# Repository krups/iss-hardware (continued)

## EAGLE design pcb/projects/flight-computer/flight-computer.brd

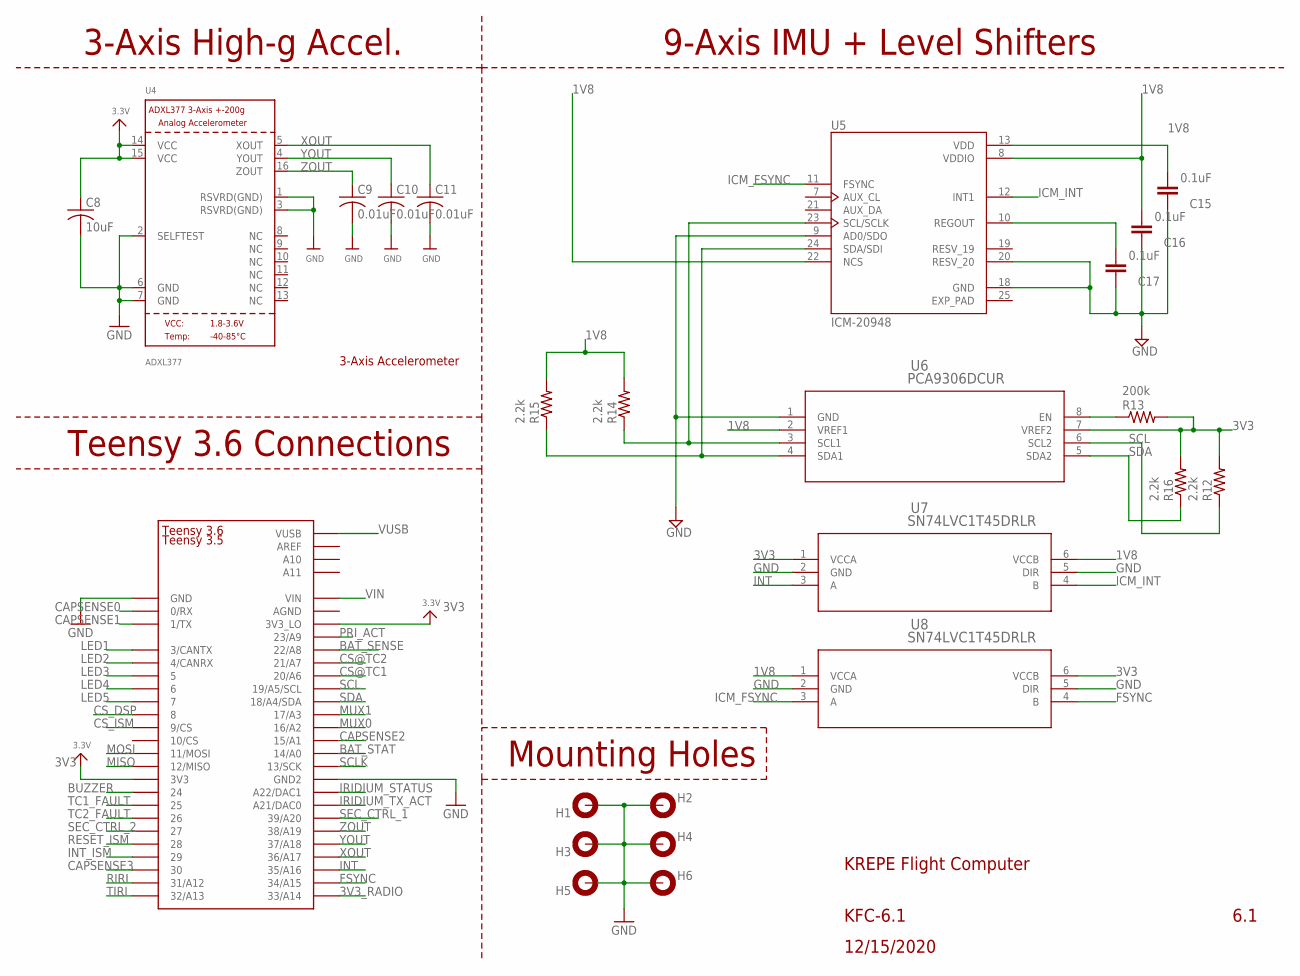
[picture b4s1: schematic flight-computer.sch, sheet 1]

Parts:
C8: 10uF; C0603
C9, C10, C11: 0.01uF; C0603
C15, C16, C17: 0.1uF; C0603
H1, H2, H3, H4, H5, H6: MOUNT-PAD-ROUND2.8; 2,8-PAD
R12, R14, R15, R16: 2.2k; R0603
R13: 200k; R0603
U4: ADXL377; LFCSP16_LQ
U5: ICM-20948; QFN40P300X300X105-25N
U6: PCA9306DCUR; DCU8
U7, U8: SN74LVC1T45DRLR; DRL6
U$1: TEENSY_3.5/3.6_BASIC

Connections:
1V8: C15.2, C16.2, R14.2, R15.2, U5.8 (VDDIO), U5.13 (VDD), U5.22 (NCS), U6.2 (VREF1), U7.6 (VCCB), U8.1 (VCCA); also elsewhere on the board
3V3: C8.1, R12.2, R13.2, R16.2, U4.14 (VCC), U4.15 (VCC), U6.7 (VREF2), U7.1 (VCCA), U8.6 (VCCB), U$1.3V3, U$1.3V3_LO; also elsewhere on the board
3V3_RADIO: U$1.33/A14; also elsewhere on the board
BAT_SENSE: U$1.22/A8; also elsewhere on the board
BAT_STAT: U$1.14/A0; also elsewhere on the board
BUZZER: U$1.24; also elsewhere on the board
CAPSENSE0: U$1.0/RX; also elsewhere on the board
CAPSENSE1: U$1.1/TX; also elsewhere on the board
CAPSENSE2: U$1.15/A1; also elsewhere on the board
CAPSENSE3: U$1.30; also elsewhere on the board
CS@TC1: U$1.20/A6; also elsewhere on the board
CS@TC2: U$1.21/A7; also elsewhere on the board
CS_DSP: U$1.8; also elsewhere on the board
CS_ISM: U$1.9/CS; also elsewhere on the board
EXP_PAD: U5.25 (EXP_PAD)
FSYNC: U8.4 (B), U$1.34/A15
GND: C8.2, C9.2, C10.2, C11.2, C15.1, C16.1, C17.1, H1.B2,8, H2.B2,8, H3.B2,8, H4.B2,8, H5.B2,8, H6.B2,8, U4.1 (RSVRD(GND)), U4.2 (SELFTEST), U4.3 (RSVRD(GND)), U4.6 (GND), U4.7 (GND), U5.9 (AD0/SDO), U5.18 (GND), U5.20 (RESV_20), U6.1 (GND), U7.2 (GND), U7.5 (DIR), U8.2 (GND), U8.5 (DIR), U$1.GND; also elsewhere on the board
ICM_FSYNC: U5.11 (FSYNC), U8.3 (A)
ICM_INT: U5.12 (INT1), U7.4 (B)
INT: U7.3 (A), U$1.35/A16
INT_ISM: U$1.29; also elsewhere on the board
IRIDIUM_STATUS: U$1.A22/DAC1; also elsewhere on the board
IRIDIUM_TX_ACT: U$1.21/DAC0 (A21/DAC0); also elsewhere on the board
LED1: U$1.3/CANTX; also elsewhere on the board
LED2: U$1.4/CANRX; also elsewhere on the board
LED3: U$1.5; also elsewhere on the board
LED4: U$1.6; also elsewhere on the board
LED5: U$1.7; also elsewhere on the board
MISO: U$1.12/MISO; also elsewhere on the board
MOSI: U$1.11/MOSI; also elsewhere on the board
MUX0: U$1.16/A2; also elsewhere on the board
MUX1: U$1.17/A3; also elsewhere on the board
unnamed: R13.1, U6.8 (EN)
unnamed: C17.2, U5.10 (REGOUT)
unnamed: R14.1, U5.23 (SCL/SCLK), U6.3 (SCL1)
unnamed: R15.1, U5.24 (SDA/SDI), U6.4 (SDA1)
PRI_ACT: U$1.23/A9; also elsewhere on the board
RESET_ISM: U$1.28; also elsewhere on the board
RIRI: U$1.31/A12; also elsewhere on the board
SCL: R12.1, U6.6 (SCL2), U$1.19/A5/SCL
SCLK: U$1.13/SCK; also elsewhere on the board
SDA: R16.1, U6.5 (SDA2), U$1.18/A4/SDA
SEC_CTRL_1: U$1.39/A20; also elsewhere on the board
SEC_CTRL_2: U$1.27; also elsewhere on the board
TC1_FAULT: U$1.25; also elsewhere on the board
TC2_FAULT: U$1.26; also elsewhere on the board
TIRI: U$1.32/A13; also elsewhere on the board
VIN: U$1.VIN; also elsewhere on the board
VUSB: U$1.VUSB; also elsewhere on the board
XOUT: C11.1, U4.5 (XOUT), U$1.36/A17
YOUT: C10.1, U4.4 (YOUT), U$1.37/A18
ZOUT: C9.1, U4.16 (ZOUT), U$1.38/A19

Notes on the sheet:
3-Axis Accelerometer
Teensy 3.5
9-Axis IMU + Level Shifters
Teensy 3.6 Connections
3-Axis High-g Accel.
Mounting Holes
KREPE Flight Computer
6.1
KFC-6.1
12/15/2020

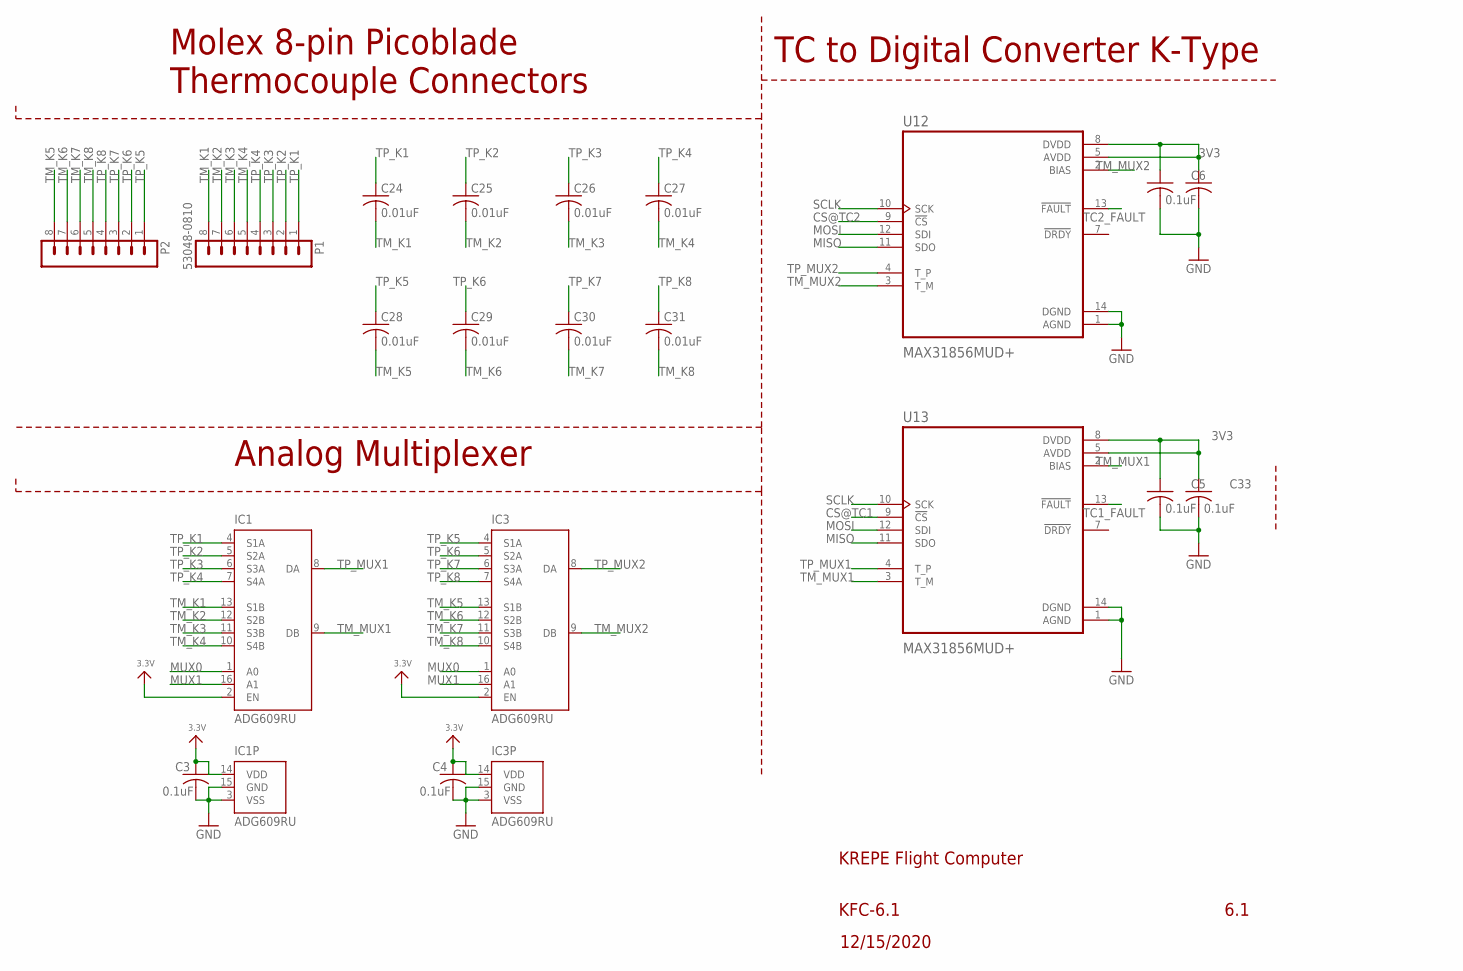
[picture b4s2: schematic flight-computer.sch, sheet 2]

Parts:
C3, C4, C5, C6, C32, C33: 0.1uF; C0603
C24, C25, C26, C27, C28, C29, C30, C31: 0.01uF; C0603
IC1, IC3: ADG609RU; TSSOP16
P1, P2: 53048-0810
U12, U13: MAX31856MUD+; SOP65P640X110-14N

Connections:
3V3: C3.1, C4.1, C5.1, C6.1, C32.1, C33.1, IC1.2 (EN), IC1.14 (VDD), IC3.2 (EN), IC3.14 (VDD), U12.5 (AVDD), U12.8 (DVDD), U13.5 (AVDD), U13.8 (DVDD); also elsewhere on the board
CS@TC1: U13.9 (!CS); also elsewhere on the board
CS@TC2: U12.9 (!CS); also elsewhere on the board
GND: C3.2, C4.2, C5.2, C6.2, C32.2, C33.2, IC1.3 (VSS), IC1.15 (GND), IC3.3 (VSS), IC3.15 (GND), U12.1 (AGND), U12.14 (DGND), U13.1 (AGND), U13.14 (DGND); also elsewhere on the board
MISO: U12.11 (SDO), U13.11 (SDO); also elsewhere on the board
MOSI: U12.12 (SDI), U13.12 (SDI); also elsewhere on the board
MUX0: IC1.1 (A0), IC3.1 (A0); also elsewhere on the board
MUX1: IC1.16 (A1), IC3.16 (A1); also elsewhere on the board
SCLK: U12.10 (SCK), U13.10 (SCK); also elsewhere on the board
TC1_FAULT: U13.13 (!FAULT); also elsewhere on the board
TC2_FAULT: U12.13 (!FAULT); also elsewhere on the board
TM_K1: C24.2, IC1.13 (S1B), P1.8
TM_K2: C25.2, IC1.12 (S2B), P1.7
TM_K3: C26.2, IC1.11 (S3B), P1.6
TM_K4: C27.2, IC1.10 (S4B), P1.5
TM_K5: C28.2, IC3.13 (S1B), P2.8
TM_K6: C29.2, IC3.12 (S2B), P2.7
TM_K7: C30.2, IC3.11 (S3B), P2.6
TM_K8: C31.2, IC3.10 (S4B), P2.5
TM_MUX1: IC1.9 (DB), U13.2 (BIAS), U13.3 (T_M)
TM_MUX2: IC3.9 (DB), U12.2 (BIAS), U12.3 (T_M)
TP_K1: C24.1, IC1.4 (S1A), P1.1
TP_K2: C25.1, IC1.5 (S2A), P1.2
TP_K3: C26.1, IC1.6 (S3A), P1.3
TP_K4: C27.1, IC1.7 (S4A), P1.4
TP_K5: C28.1, IC3.4 (S1A), P2.1
TP_K6: C29.1, IC3.5 (S2A), P2.2
TP_K7: C30.1, IC3.6 (S3A), P2.3
TP_K8: C31.1, IC3.7 (S4A), P2.4
TP_MUX1: IC1.8 (DA), U13.4 (T_P)
TP_MUX2: IC3.8 (DA), U12.4 (T_P)

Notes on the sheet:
Analog Multiplexer
TC to Digital Converter K-Type
Molex 8-pin Picoblade Thermocouple Connectors
6.1
KFC-6.1
12/15/2020
KREPE Flight Computer

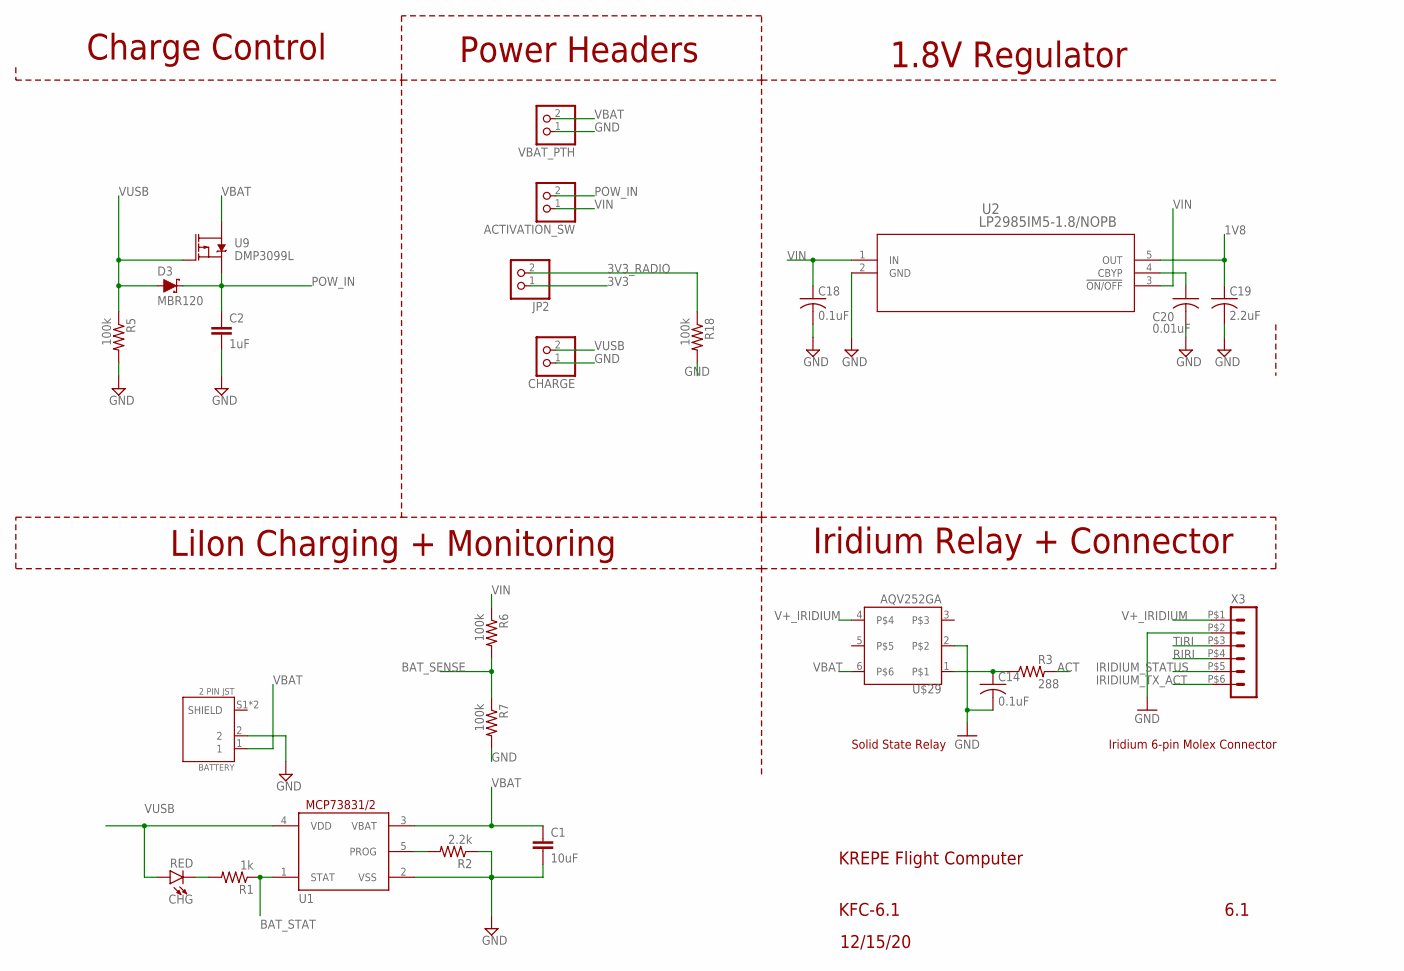
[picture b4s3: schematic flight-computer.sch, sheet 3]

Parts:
ACTIVATION_SW: PINHD-1X2; 1X02
BATTERY: 2 PIN JST; JST_S2B-PH-SM4-TB(LF)(SN)
C1: 10uF; C0603
C2: 1uF; C0603
C14, C18: 0.1uF; C0603
C19: 2.2uF; C0603
C20: 0.01uF; C0603
CHARGE: PINHD-1X2; 1X02
CHG: RED; LED-0603
D3: MBR120; SOD123FL
JP2: PINHD-1X2; 1X02
R1: 1k; R0603
R2: 2.2k; R0603
R3: 288; R0603
R5, R6, R7, R18: 100k; R0603
U1: MCP73831/OT; SOT23-5L
U2: LP2985IM5-1.8/NOPB; MF05A
U9: DMP3099L; SOT23
U$29: AQV252GA; DIP6
VBAT_PTH: PINHD-1X2; 1X02
X3: HEADER_POS6_43650-0600; 43650-0600

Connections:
1V8: C19.1, U2.5 (OUT); also elsewhere on the board
3V3: JP2.1; also elsewhere on the board
3V3_RADIO: JP2.2, R18.1; also elsewhere on the board
ACT: R3.2; also elsewhere on the board
BAT_SENSE: R6.2, R7.1; also elsewhere on the board
BAT_STAT: R1.1, U1.1 (STAT); also elsewhere on the board
GND: BATTERY.2, C1.2, C2.2, C14.2, C18.2, C19.2, C20.2, CHARGE.1, R2.1, R5.2, R7.2, R18.2, U1.2 (VSS), U2.2 (GND), U$29.2, VBAT_PTH.1, X3.P$2 (2); also elsewhere on the board
IRIDIUM_STATUS: X3.P$5 (5); also elsewhere on the board
IRIDIUM_TX_ACT: X3.P$6 (6); also elsewhere on the board
unnamed: R2.2, U1.5 (PROG)
unnamed: C14.1, R3.1, U$29.1
unnamed: CHG.C, R1.2
unnamed: C20.1, U2.4 (CBYP)
POW_IN: ACTIVATION_SW.2, C2.1, D3.C, U9.2 (S)
RIRI: X3.P$4 (4); also elsewhere on the board
TIRI: X3.P$3 (3); also elsewhere on the board
V+_IRIDIUM: U$29.4, X3.P$1 (1)
VBAT: BATTERY.1, C1.1, U1.3 (VBAT), U9.3 (D), U$29.6, VBAT_PTH.2
VIN: ACTIVATION_SW.1, C18.1, R6.1, U2.1 (IN), U2.3 (!ON/OFF); also elsewhere on the board
VUSB: CHARGE.2, CHG.A, D3.A, R5.1, U1.4 (VDD), U9.1 (G); also elsewhere on the board

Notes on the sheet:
Iridium 6-pin Molex Connector
Solid State Relay
Iridium Relay + Connector
Charge Control
Power Headers
LiIon Charging + Monitoring
1.8V Regulator
6.1
KFC-6.1
12/15/20
KREPE Flight Computer

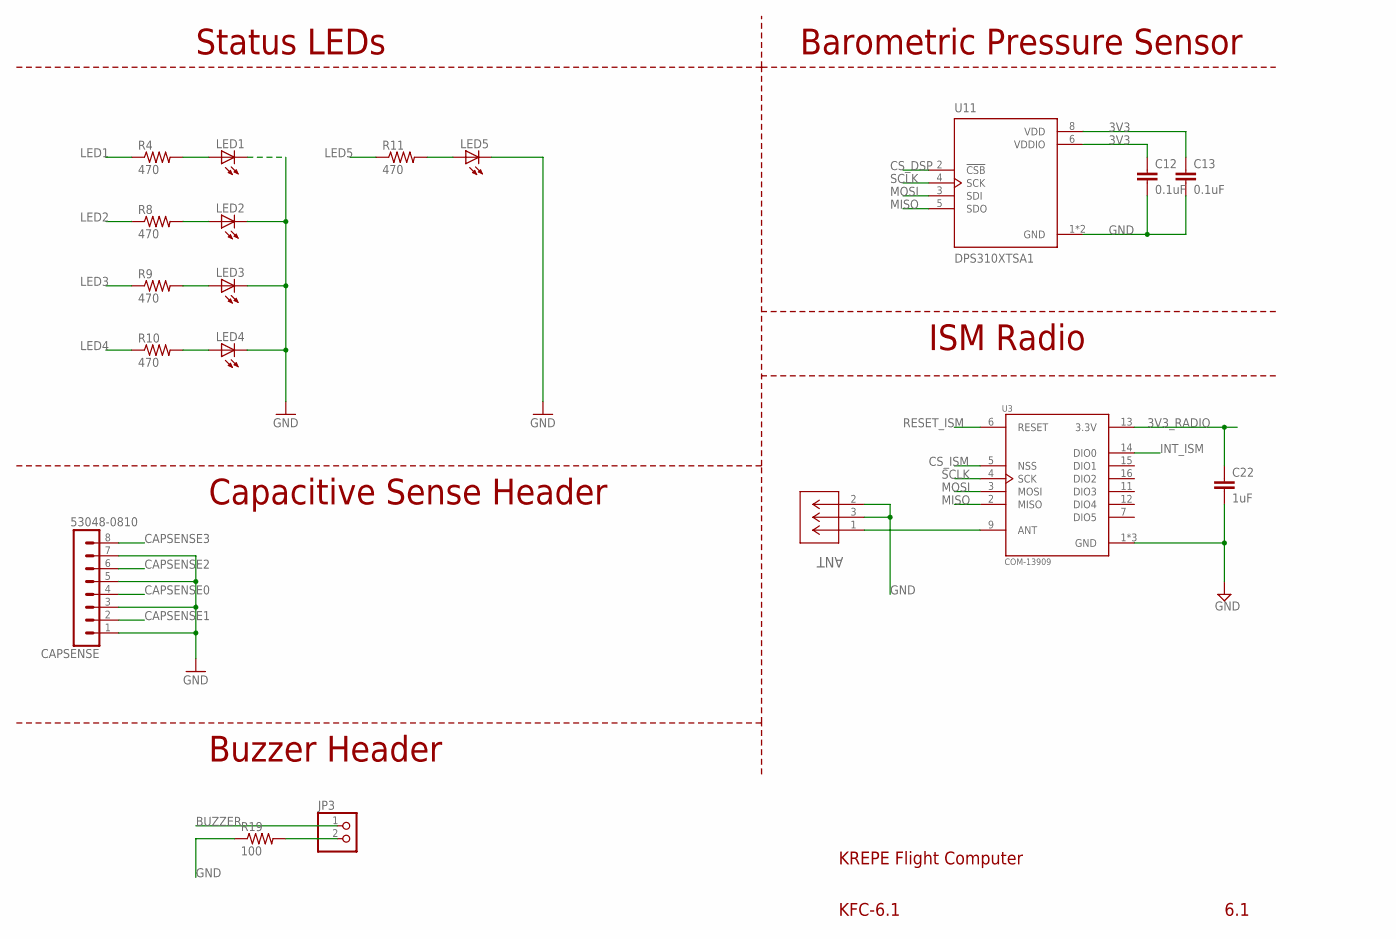
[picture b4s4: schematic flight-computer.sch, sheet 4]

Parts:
ANT: U.FL-R-SMT-1(10); CONN_R-SMT-1(10)
C12, C13: 0.1uF; C0603
C22: 1uF; C0603
CAPSENSE: 53048-0810
JP3: PINHD-1X2; 1X02
LED1, LED2, LED3, LED4, LED5: LEDCHIP-LED0603; CHIP-LED0603
R4, R8, R9, R10, R11: 470; R0603
R19: 100; R0603
U3: COM-13909; MOD_COM-13909
U11: DPS310XTSA1; XDCR_DPS310XTSA1

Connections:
3V3: C12.1, C13.1, U11.6 (VDDIO), U11.8 (VDD); also elsewhere on the board
3V3_RADIO: C22.1, U3.13 (3.3V); also elsewhere on the board
BUZZER: JP3.1; also elsewhere on the board
CAPSENSE0: CAPSENSE.4; also elsewhere on the board
CAPSENSE1: CAPSENSE.2; also elsewhere on the board
CAPSENSE2: CAPSENSE.6; also elsewhere on the board
CAPSENSE3: CAPSENSE.8; also elsewhere on the board
CS_DSP: U11.2 (!CSB); also elsewhere on the board
CS_ISM: U3.5 (NSS); also elsewhere on the board
GND: ANT.2, ANT.3, C12.2, C13.2, C22.2, CAPSENSE.1, CAPSENSE.3, CAPSENSE.5, CAPSENSE.7, LED1.C, LED2.C, LED3.C, LED4.C, LED5.C, R19.1, U3.1 (GND), U3.8 (GND), U3.10 (GND), U11.1 (GND), U11.7 (GND); also elsewhere on the board
INT_ISM: U3.14 (DIO0); also elsewhere on the board
LED1: R4.1; also elsewhere on the board
LED2: R8.1; also elsewhere on the board
LED3: R9.1; also elsewhere on the board
LED4: R10.1; also elsewhere on the board
LED5: R11.1; also elsewhere on the board
MISO: U3.2 (MISO), U11.5 (SDO); also elsewhere on the board
MOSI: U3.3 (MOSI), U11.3 (SDI); also elsewhere on the board
unnamed: JP3.2, R19.2
unnamed: ANT.1, U3.9 (ANT)
unnamed: LED1.A, R4.2
unnamed: LED2.A, R8.2
unnamed: LED3.A, R9.2
unnamed: LED4.A, R10.2
unnamed: LED5.A, R11.2
RESET_ISM: U3.6 (RESET); also elsewhere on the board
SCLK: U3.4 (SCK), U11.4 (SCK); also elsewhere on the board

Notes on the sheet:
ISM Radio
6.1
Status LEDs
Capacitive Sense Header
Buzzer Header
Barometric Pressure Sensor
KFC-6.1
KREPE Flight Computer

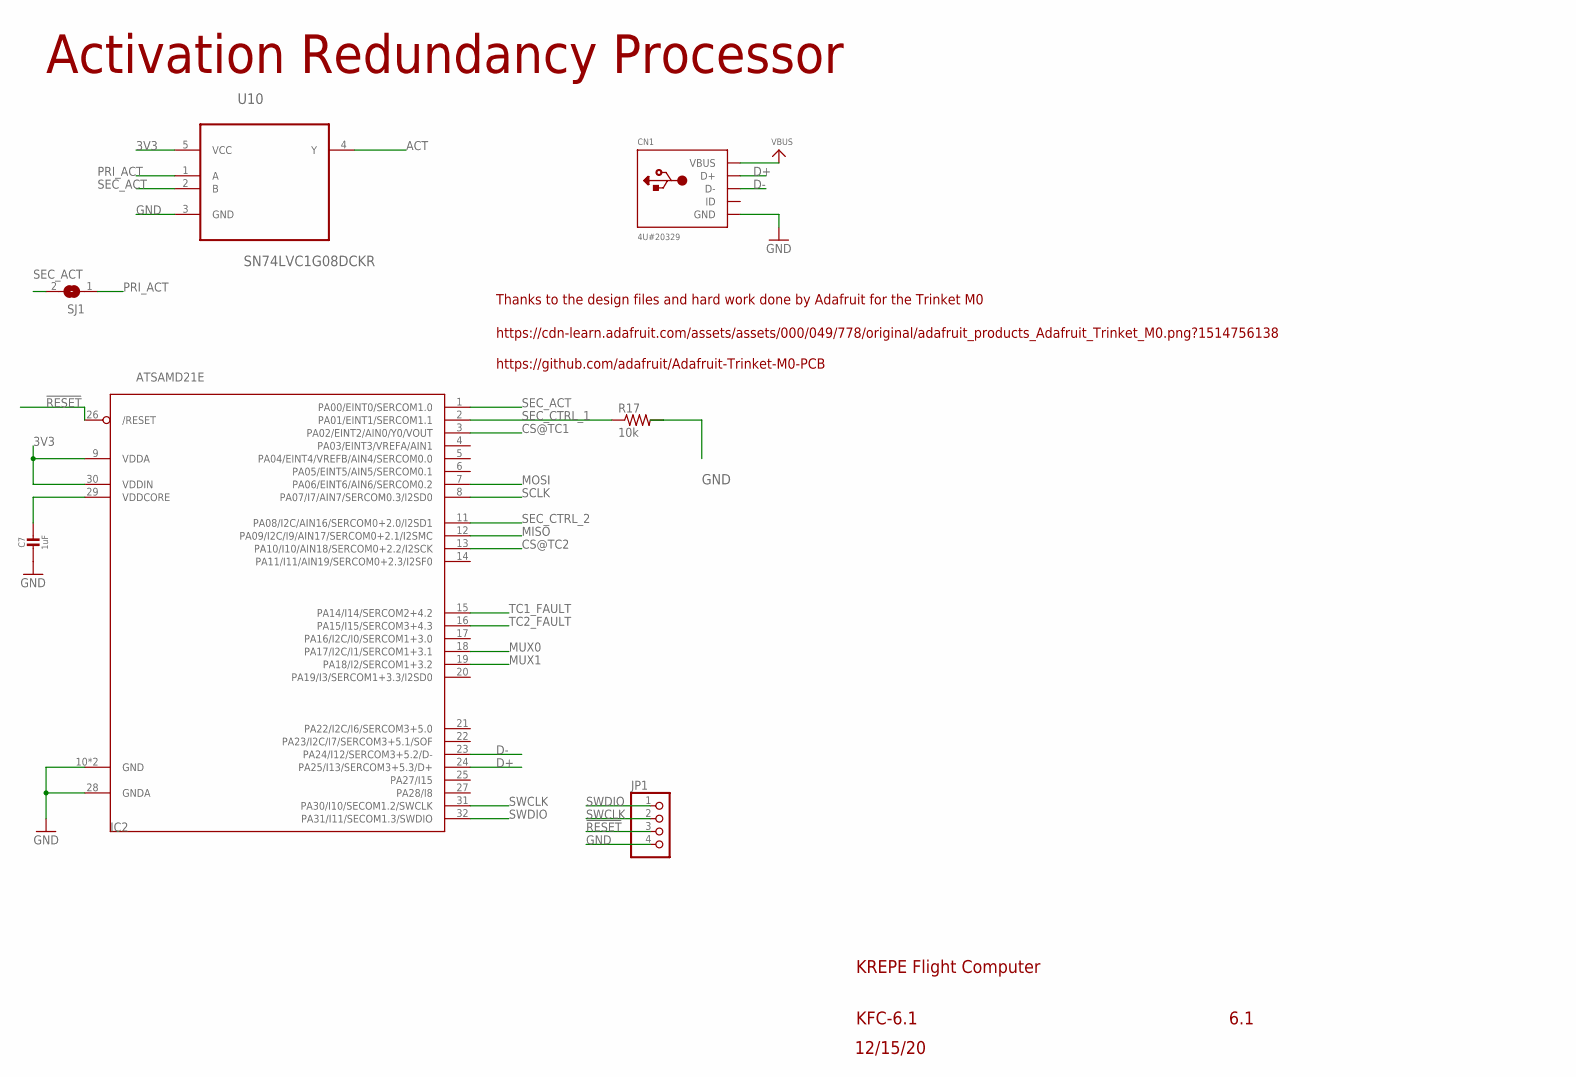
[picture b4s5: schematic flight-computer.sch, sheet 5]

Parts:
C7: 1uF; 0603-NO
CN1: 4U#20329; 4UCONN_20329_V2
IC2: ATSAMD21E; QFN32_5MM
JP1: PINHD-1X4; 1X04
R17: 10k; R0603
SJ1: SJ
U10: SN74LVC1G08DCKR; SOT65P210X110-5N

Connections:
3V3: IC2.9 (VDDA), IC2.30 (VDDIN), U10.5 (VCC); also elsewhere on the board
!RESET: IC2.26 (/RESET), JP1.3
ACT: U10.4 (Y); also elsewhere on the board
CS@TC1: IC2.3 (PA02/EINT2/AIN0/Y0/VOUT); also elsewhere on the board
CS@TC2: IC2.13 (PA10/I10/AIN18/SERCOM0+2.2/I2SCK); also elsewhere on the board
D+: CN1.D+, IC2.24 (PA25/I13/SERCOM3+5.3/D+)
D-: CN1.D-, IC2.23 (PA24/I12/SERCOM3+5.2/D-)
GND: C7.2, CN1.BASE@1 (GND), CN1.BASE@2 (GND), CN1.GND, CN1.SPRT@1 (GND), CN1.SPRT@2 (GND), CN1.SPRT@3 (GND), CN1.SPRT@4 (GND), IC2.10 (GND), IC2.28 (GNDA), IC2.33 (GND), JP1.4, R17.2, U10.3 (GND); also elsewhere on the board
MISO: IC2.12 (PA09/I2C/I9/AIN17/SERCOM0+2.1/I2SMC); also elsewhere on the board
MOSI: IC2.7 (PA06/EINT6/AIN6/SERCOM0.2); also elsewhere on the board
MUX0: IC2.18 (PA17/I2C/I1/SERCOM1+3.1); also elsewhere on the board
MUX1: IC2.19 (PA18/I2/SERCOM1+3.2); also elsewhere on the board
PRI_ACT: SJ1.1, U10.1 (A); also elsewhere on the board
SCLK: IC2.8 (PA07/I7/AIN7/SERCOM0.3/I2SD0); also elsewhere on the board
SEC_ACT: IC2.1 (PA00/EINT0/SERCOM1.0), SJ1.2, U10.2 (B)
SEC_CTRL_1: IC2.2 (PA01/EINT1/SERCOM1.1), R17.1; also elsewhere on the board
SEC_CTRL_2: IC2.11 (PA08/I2C/AIN16/SERCOM0+2.0/I2SD1); also elsewhere on the board
SWCLK: IC2.31 (PA30/I10/SECOM1.2/SWCLK), JP1.2
SWDIO: IC2.32 (PA31/I11/SECOM1.3/SWDIO), JP1.1
TC1_FAULT: IC2.15 (PA14/I14/SERCOM2+4.2); also elsewhere on the board
TC2_FAULT: IC2.16 (PA15/I15/SERCOM3+4.3); also elsewhere on the board
VBUS: CN1.VBUS
VDDCORE1: C7.1, IC2.29 (VDDCORE)

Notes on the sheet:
Activation Redundancy Processor
Thanks to the design files and hard work done by Adafruit for the Trinket M0
https://cdn-learn.adafruit.com/assets/assets/000/049/778/original/adafruit_products_Adafruit_Trinket_M0.png?1514756138 https://github.com/adafruit/Adafruit-Trinket-M0-PCB
KFC-6.1
KREPE Flight Computer
12/15/20
6.1

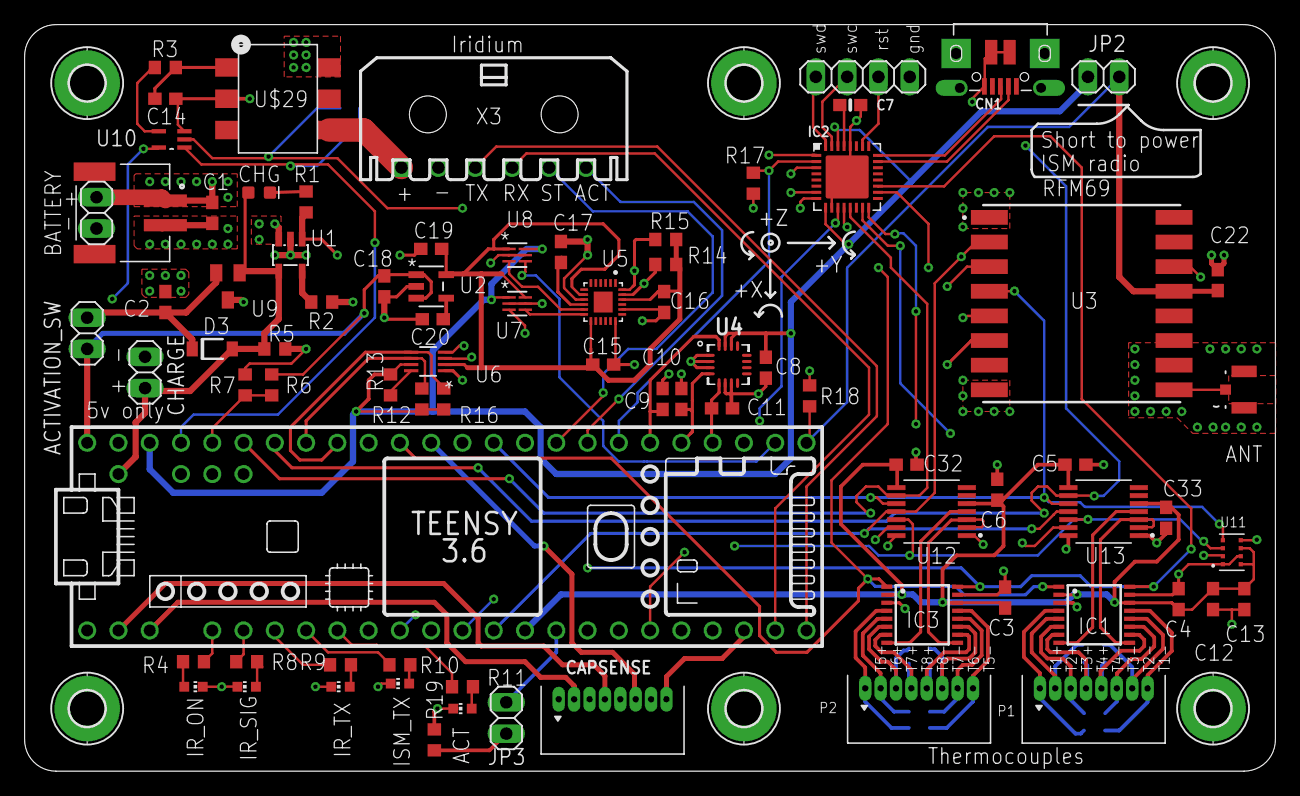
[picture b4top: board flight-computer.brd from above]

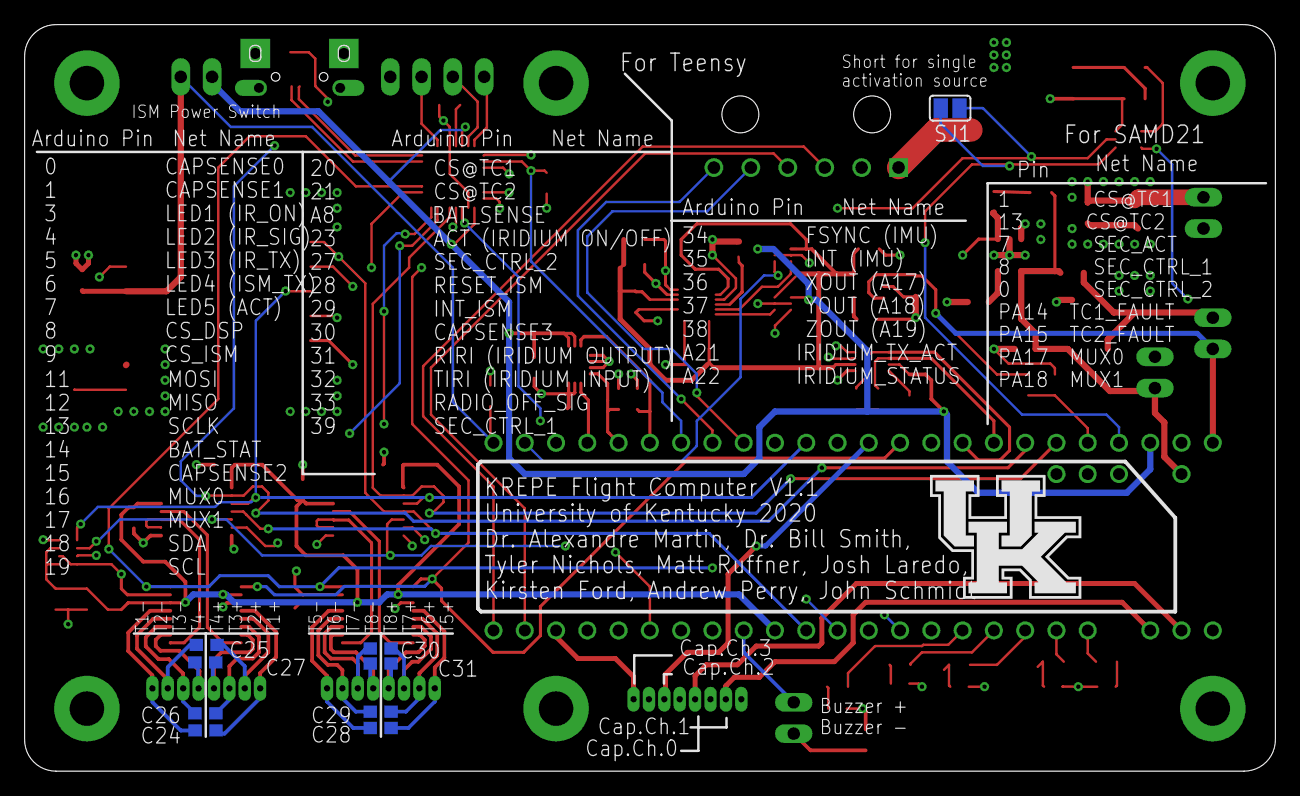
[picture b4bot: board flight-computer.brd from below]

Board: 4 copper layers, 101.6 x 60.6 mm, 95 parts (9 on the bottom side), 93 nets.

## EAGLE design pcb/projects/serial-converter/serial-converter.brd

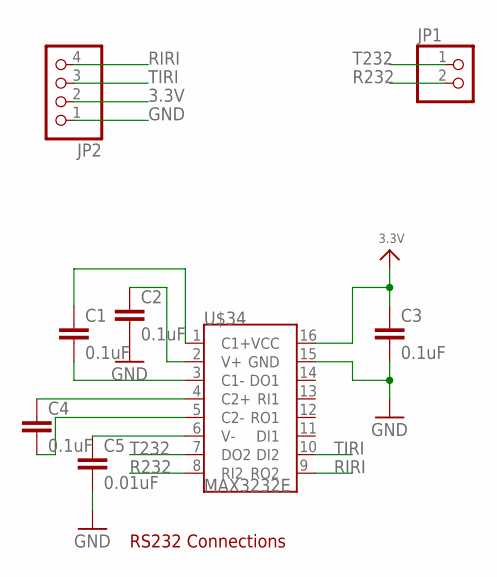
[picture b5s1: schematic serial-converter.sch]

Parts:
C1, C2, C3, C4: 0.1uF; C0603
C5: 0.01uF; C0603
JP1: PINHD-1X2; 1X02
JP2: PINHD-1X4; 1X04
U$34: MAX3232E; SSOP-16

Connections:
3.3V: C3.1, JP2.2, U$34.16 (VCC)
GND: C2.2, C3.2, C5.2, JP2.1, U$34.15 (GND)
unnamed: C1.1, U$34.1 (C1+)
unnamed: C1.2, U$34.3 (C1-)
unnamed: C4.1, U$34.4 (C2+)
unnamed: C4.2, U$34.5 (C2-)
unnamed: C5.1, U$34.6 (V-)
unnamed: C2.1, U$34.2 (V+)
R232: JP1.2, U$34.8 (RI2)
RIRI: JP2.4, U$34.9 (RO2)
T232: JP1.1, U$34.7 (DO2)
TIRI: JP2.3, U$34.10 (DI2)

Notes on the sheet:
RS232 Connections

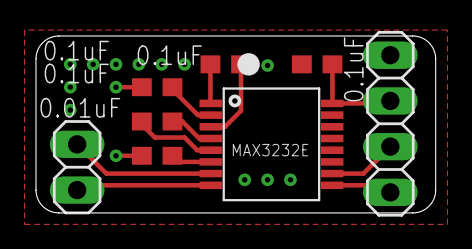
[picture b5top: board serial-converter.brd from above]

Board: 2 copper layers, 22.2 x 9.8 mm, 8 parts (0 on the bottom side), 12 nets.

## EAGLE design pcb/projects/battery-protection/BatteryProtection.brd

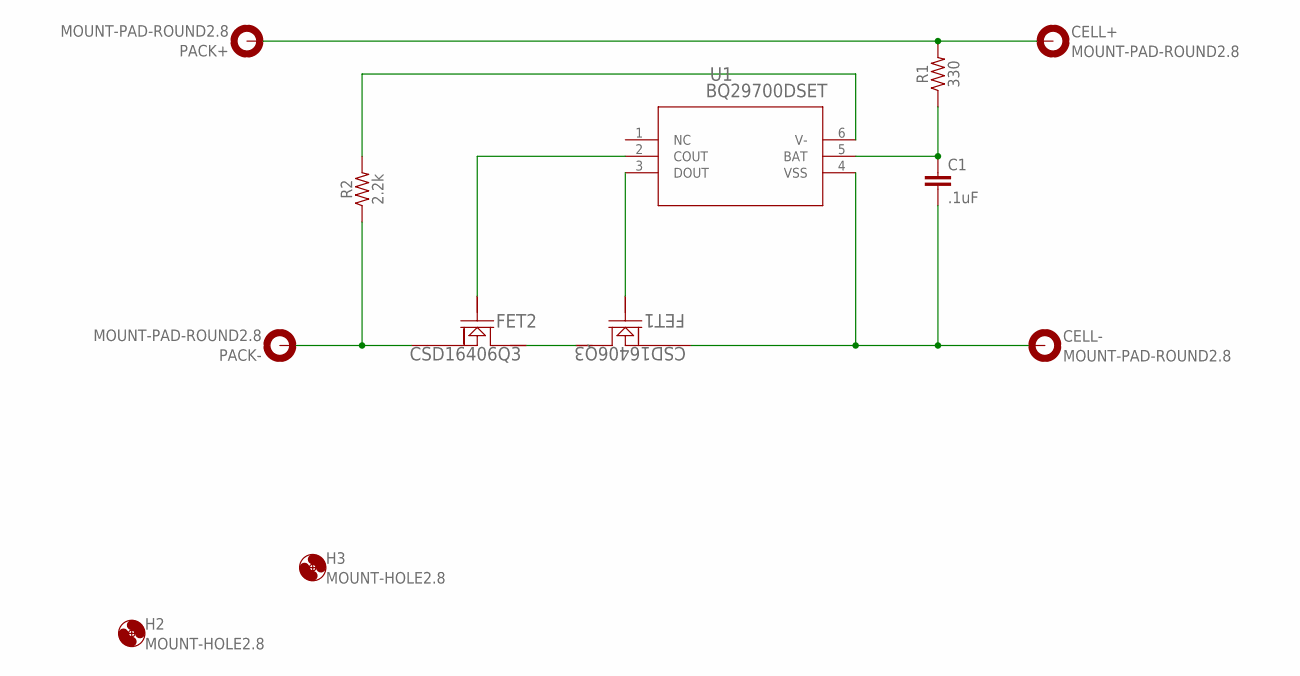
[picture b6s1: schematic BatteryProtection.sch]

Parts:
C1: .1uF; 0805
CELL+: MOUNT-PAD-ROUND2.8; 2,8-PAD
CELL-: MOUNT-PAD-ROUND2.8; 2,8-PAD
FET1, FET2: CSD16406Q3; DQG0008A
H2, H3: MOUNT-HOLE2.8; 2,8
PACK+: MOUNT-PAD-ROUND2.8; 2,8-PAD
PACK-: MOUNT-PAD-ROUND2.8; 2,8-PAD
R1: 330; 0603
R2: 2.2k; 0603
U1: BQ29700DSET; DSE6

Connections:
unnamed: C1.1, R1.1, U1.5 (BAT)
unnamed: FET2.4 (GATE), U1.2 (COUT)
unnamed: C1.2, CELL-.B2,8, FET1.1 (SOURCE), U1.4 (VSS)
unnamed: FET1.5 (DRAIN_2), FET2.5 (DRAIN_2)
unnamed: FET1.4 (GATE), U1.3 (DOUT)
unnamed: R2.2, U1.6 (V-)
unnamed: CELL+.B2,8, PACK+.B2,8, R1.2
unnamed: FET2.1 (SOURCE), PACK-.B2,8, R2.1

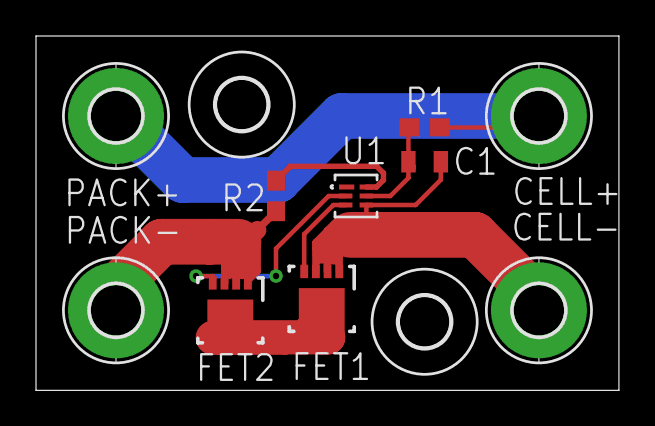
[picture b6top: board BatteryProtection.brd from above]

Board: 2 copper layers, 32.4 x 19.7 mm, 12 parts (0 on the bottom side), 8 nets.

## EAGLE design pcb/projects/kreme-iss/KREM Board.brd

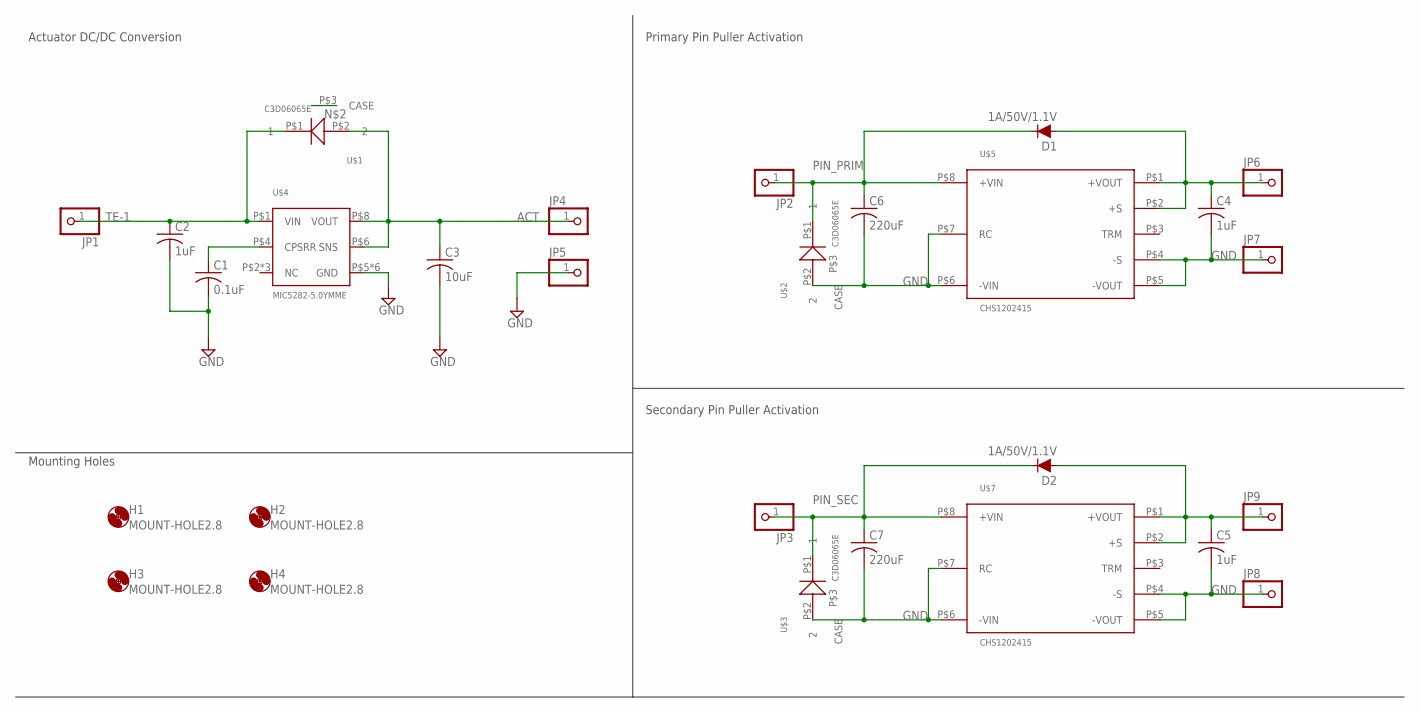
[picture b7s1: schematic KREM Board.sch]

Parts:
C1: 0.1uF; C2220K
C2, C4, C5: 1uF; C2220K
C3: 10uF; C2220K
C6, C7: 220uF; C2220K
D1, D2: 1A/50V/1.1V; DIODE-1N4001-KIT
H1, H2, H3, H4: MOUNT-HOLE2.8; 2,8
JP1, JP2, JP3, JP4, JP5, JP6, JP7, JP8, JP9: PINHD-1X1; 1X01
U$1, U$2, U$3: C3D06065E; TO-252
U$4: MIC5282-5.0YMME; MSOP8-EPAD
U$5, U$7: CHS1202415

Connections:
ACT: C3.1, JP4.1, U$1.P$2 (2), U$4.P$6 (SNS), U$4.P$8 (VOUT)
GND: C1.2, C2.2, C3.2, C4.2, C5.2, C6.2, C7.2, JP5.1, JP7.1, JP8.1, U$2.P$2 (2), U$3.P$2 (2), U$4.P$5 (GND), U$4.P$9 (GND), U$4.P$10 (GND), U$4.P$11 (GND), U$4.P$12 (GND), U$4.P$13 (GND), U$5.P$4 (-S), U$5.P$5 (-VOUT), U$5.P$6 (-VIN), U$5.P$7 (RC), U$7.P$4 (-S), U$7.P$5 (-VOUT), U$7.P$6 (-VIN), U$7.P$7 (RC)
unnamed: C1.1, U$4.P$4 (CPSRR)
unnamed: C4.1, D1.A, JP6.1, U$5.P$1 (+VOUT), U$5.P$2 (+S)
unnamed: C5.1, D2.A, JP9.1, U$7.P$1 (+VOUT), U$7.P$2 (+S)
PIN_PRIM: C6.1, D1.C, JP2.1, U$2.P$1 (1), U$5.P$8 (+VIN)
PIN_SEC: C7.1, D2.C, JP3.1, U$3.P$1 (1), U$7.P$8 (+VIN)
TE-1: C2.1, JP1.1, U$1.P$1 (1), U$4.P$1 (VIN)

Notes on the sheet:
Actuator DC/DC Conversion
Primary Pin Puller Activation
Secondary Pin Puller Activation
Mounting Holes

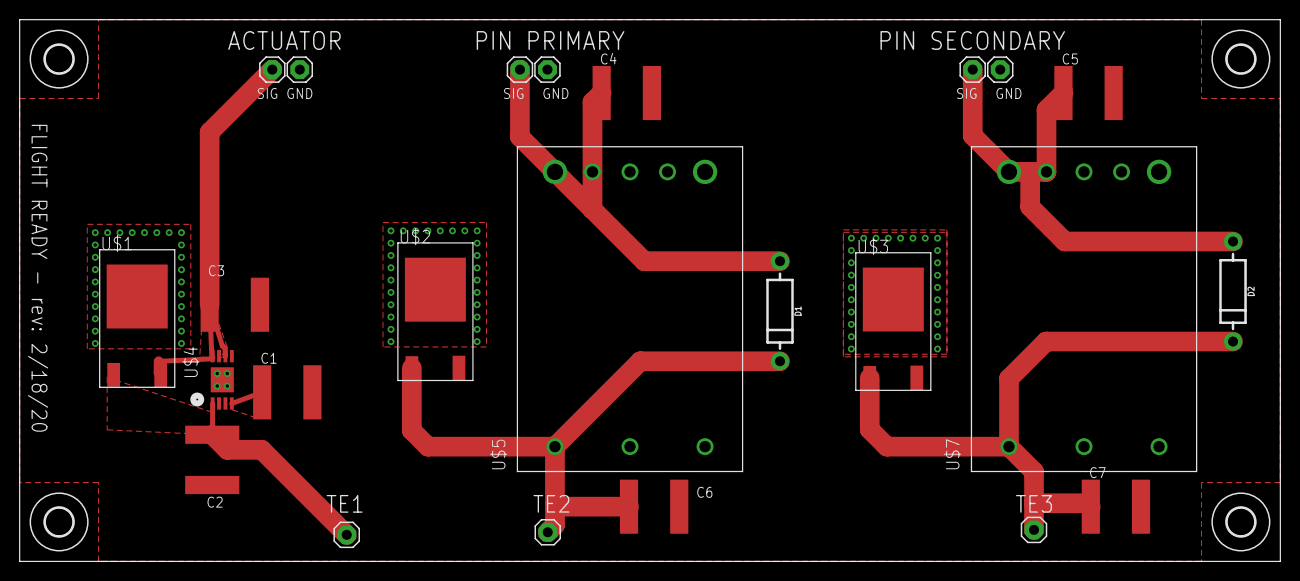
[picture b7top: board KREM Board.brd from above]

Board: 2 copper layers, 128.0 x 55.0 mm, 28 parts (0 on the bottom side), 8 nets.

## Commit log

2020-03-30 v1 pcb and documentation
2020-03-30 moved image with dimensions
2020-03-30 added renders of top and bottom
2020-03-31 updated dxf
2020-03-31 created projects folder
2020-05-30 update and add battery protection test board
2020-06-29 v1.1 update
    Updates to the flight computer:
    * update to max31856 tc to digital to support k/j type tc as well as 7
    other types
    * add pins for iridium sbd message ready and iridium actively
    transmitting
    * add capacity sense header
2020-07-01 add fault signal from tc converter
    - add the respective pins to the arduino pinmap
    - update doc pdf and schematic screenshots
2020-07-01 add digikey BOM for v1.1
2020-07-04 add activation redundancy processor
    - partial update of documentation to reflect this addition
    - extra diagram of redundant activation
    - pcb update to include a 32 pin qfn samd21 cortex m0 processor and necessary connections to bootload and flash over USB
2020-07-06 updated documentation, BOM and pinmap for activation redundancy processor
2020-07-24 add v1.1 pcb and documentation - added DSP310 barometric pressure sensor - add buzzer - add capacitive sense header - add more interface pins to the safety processor - add arduino pinouts for safety 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
2020-07-24 fix indentation
2020-07-24 update v1.1 digikey BOM
2021-01-23 documentation update
2021-01-23 add serial converter files
2021-01-23 add battery protection schematic
2021-01-23 add document revision
2021-02-11 update for phase 3 safety review
2021-03-05 fix wire gauge in fig. 1. add tr-01 testing report
2022-09-16 add initial layout, schematic and libraries for KREPE-2 flight computer revision
2022-09-16 updates to layout
2022-09-20 update PCB and libraries
2022-09-20 silk update
2022-10-12 added spectrometer breakout
2022-10-12 update libraries and v2 flight comp
2022-11-15 v2 cam files, renderings, and datasheets
2022-11-22 update images in hardware manual, update diagrams
2022-11-24 add avionics diagram
2023-01-03 add ssr to flight computer. add to hardware manual
2023-01-13 v2.1 flight computer update. add pressure sensor breakout. add schematic pdfs
2023-02-14 add battery tabbing spec. cam files for pressure sensor breakout. final schematics for v2.1 as ordered.
2023-09-06 flight computer hardware manual updates
2024-09-27 add build images and latest schematic from EAGLE
